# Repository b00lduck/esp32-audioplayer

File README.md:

# esp32-audioplayer
ESP32 based MP3 audio player with RFID control and case made from laser cutted plywood

!!! WORK IN PROGRESS !!!
!!! not functional yet !!!

## Used electronic hardware components:
* ESP32 NodeMCU module
* RFID-RC522 module (i.e. https://www.ebay.de/itm/172603664748)
* VS1053B module with SD-slot (i.e. http://www.ebay.de/itm/272761135002)
* Mifare classic 13.56MHz RFID cards (clones will do the job too, i.e. http://www.ebay.de/itm/122525501095)
* Adafruit PowerBoost 500 Charger module
* 3.7V LiPo battery 
* Class-D amplifier module
* SD-Card (i.e. 4GB)
* two Visaton FR7 (4 ohms) speakers
* Custom main board (see kicad folder for layout)
* Custom panel board (see kicad folder for layout)
* 1x 220uF 35V
* 1x 1uF 63V
* 4x 100nF 
* 2x 47nF
* 1x resistor ladder 4x 4.7k
* 1x 10R 
* 1x 10kR
* 1x 22kR
* 4x WSL10 (2x5 header 2.54mm with notch)
* 2x 2-pin header 2.54mm
* 4x 4-pin header 2.54mm
* some wire for airwires
* some insulated wire 1mm², red and black (for internal connections)
* 1x USB 2 Micro-B connector
* 1x power switch
* 1x USB 2 micro cable (for internal connection)
* optional: MEMS gyroscope module
* optional: 0.96 inch I2C OLED display

## Wood parts:
* 6 sheets, one for every side of the case
* 2 distance rings for the speakers

## Metal parts:
* 2x 100x75x0.8mm aluminium sheet

## 3D-Printed parts:
* 8x inner edge reinforcements
* 4x M3x3 standoff
* 8x M3*8 standoff (for main board)
* 4x M3x11 standoff (for MP3 board)
* 2x M3x6 standoff (for panel board)
* 2x M3x4 standoff (for panel board)
* 1x USB receptacle holder
* 1x SD-Card slot box
* 1x SD-Card slot cover

## Screws
* 4x M3x25 DIN 7991/ISO 10642 (countersunk allen bolt)
* 32x M3 DIN 934/ISO 4042 (nut)
* 8x M3 DIN 125/ISO 7089 (washer)
* 8x M3x20 DIN 912/ISO 4762 (cylinder head allen bolt)
* 2x M2x10 DIN 912/ISO 4762 (cylinder head allen bolt) for amp
* 2x M2 DIN 934/ISO 4042 (nut)
* 2x M2 DIN 125/ISO 7089 (washer)
* 8x M3x?? DIN 7991/ISO 10642 (countersunk allen bolt) for speakers
* 24x M3x15 DIN 7991/ISO 10642 (countersunk allen bolt) for inner corners

## Used software:
* VSCode with PlatformioIDE

## Used Arduino Libraries:
* SdFat 1.0.7
* MFRC522 1.3.6

## Port mapping
see src/config.h

## 3D printing
I used black 1.75 PETG filament for all parts.
Layer height was 0.15mm at a printing speed of 30mm/s.

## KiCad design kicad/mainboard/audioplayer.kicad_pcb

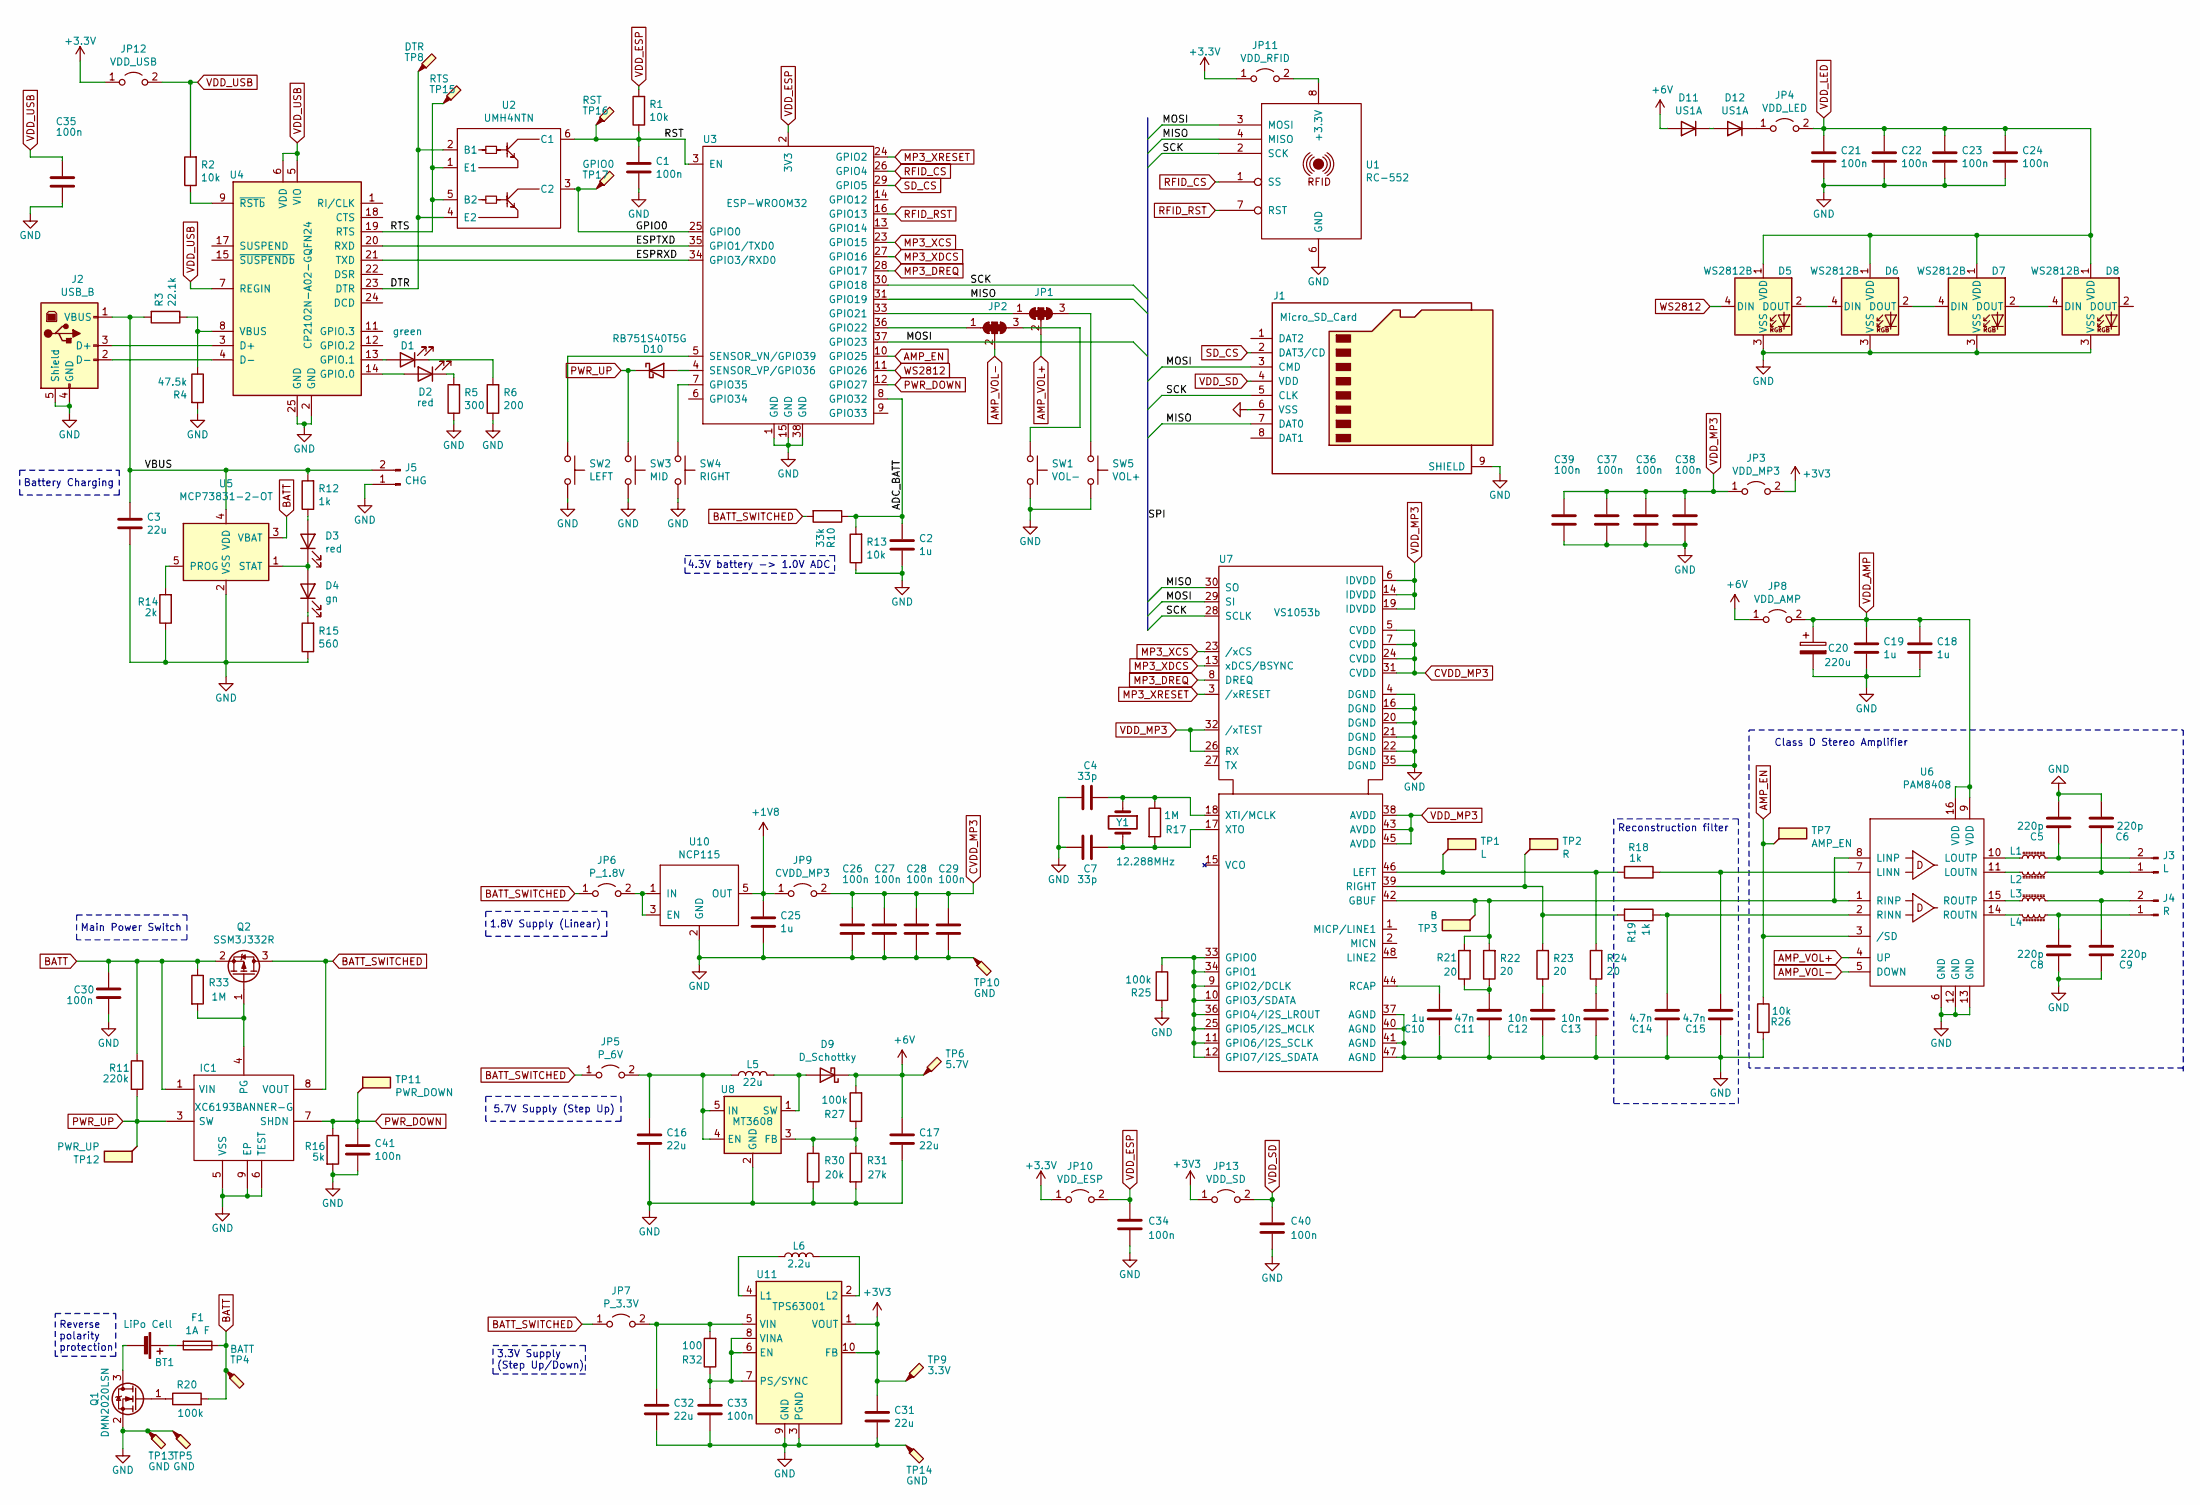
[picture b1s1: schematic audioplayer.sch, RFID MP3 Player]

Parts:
BT1: LiPo Cell; PinHeader_1x02_P2.54mm_Vertical
C1, C21, C22, C23, C24, C26, C27, C28, C29, C30, C33, C34, C35, C36, C37, C38, C39, C40, C41: 100n; C_0603_1608Metric
C2, C10, C18, C19, C25: 1u; C_0805_2012Metric; Mouser 963-EMK212B7105KG-T
C3, C16, C17, C31, C32: 22u; C_1210_3225Metric; Mouser 963-EMK325B7226MMHP
C4, C7: 33p; C_0603_1608Metric
C5, C6, C8, C9: 220p; C_0603_1608Metric
C11: 47n; C_0805_2012Metric; Mouser 80-C0805C473J3GEAULR
C12, C13: 10n; C_0603_1608Metric; Mouser 81-GRM1885C1E103JA1D
C14, C15: 4.7n; C_0603_1608Metric; Farnell 2906783
C20: 220u; CP_Radial_D8.0mm_P3.50mm
D1: green; LED_0805_2012Metric; Farnell 1318243
D2: red; LED_0805_2012Metric; Farnell 1318244
D3: red; LED_0805_2012Metric; Farnell 1318243
D4: gn; LED_0805_2012Metric; Farnell 1318244
D5, D6, D7, D8: WS2812B; LED_WS2812B_PLCC4_5.0x5.0mm_P3.2mm
D9: D_Schottky; D_SMA; Farnell 2211964
D10: RB751S40T5G; D_SOD-523; Farnell 2211964
D11, D12: US1A; D_SMA
F1: 1A F; Fuse_Littelfuse_372_D8.50mm
IC1: XC6193BANNER-G; XC6192AA05ERG
J1: Micro_SD_Card; microSD_HC_Hirose_DM3AT-SF-PEJM5; Farnell 1764374
J2: USB_B; USB_B_Lumberg_2411_02_Horizontal; Farnell 1308876
J3: L; PinHeader_1x02_P2.54mm_Vertical
J4: R; PinHeader_1x02_P2.54mm_Vertical
J5: CHG; PinHeader_1x02_P2.54mm_Vertical
JP1, JP2: SolderJumper_3_Bridged123; SolderJumper-3_P1.3mm_Open_RoundedPad1.0x1.5mm_NumberLabels
JP3: VDD_MP3; SolderJumper-2_P1.3mm_Open_RoundedPad1.0x1.5mm
JP4: VDD_LED; SolderJumper-2_P1.3mm_Open_RoundedPad1.0x1.5mm
JP5: P_6V; SolderJumper-2_P1.3mm_Open_RoundedPad1.0x1.5mm
JP6: P_1.8V; SolderJumper-2_P1.3mm_Open_RoundedPad1.0x1.5mm
JP7: P_3.3V; SolderJumper-2_P1.3mm_Open_RoundedPad1.0x1.5mm
JP8: VDD_AMP; SolderJumper-2_P1.3mm_Open_RoundedPad1.0x1.5mm
JP9: CVDD_MP3; SolderJumper-2_P1.3mm_Open_RoundedPad1.0x1.5mm
JP10: VDD_ESP; SolderJumper-2_P1.3mm_Open_RoundedPad1.0x1.5mm
JP11: VDD_RFID; SolderJumper-2_P1.3mm_Open_RoundedPad1.0x1.5mm
JP12: VDD_USB; SolderJumper-2_P1.3mm_Open_RoundedPad1.0x1.5mm
JP13: VDD_SD; SolderJumper-2_P1.3mm_Open_RoundedPad1.0x1.5mm
L1, L2, L3, L4: 600; L_0805_2012Metric; Farnell 1635719
L5: 22u; L_Taiyo-Yuden_NR-60xx; Mouser 963-NR6028T220M
L6: 2.2u; L_Taiyo-Yuden_NR-60xx; Mouser 963-NR6028T2R2N
Q1: DMN2020LSN; SC-59; Farnell 2543536
Q2: SSM3J332R; SOT-23
R1, R2, R13, R26: 10k; R_0603_1608Metric
R3: 22.1k; R_1206_3216Metric; Mouser 71-CRCW120622K1FKEAC
R4: 47.5k; R_1206_3216Metric; Mouser 71-CRCW120647K5FKEAC
R5: 300; R_0603_1608Metric
R6: 200; R_0603_1608Metric
R10: 33k; R_0603_1608Metric
R11: 220k; R_0603_1608Metric
R12, R18, R19: 1k; R_0603_1608Metric
R14: 2k; R_0603_1608Metric
R15: 560; R_0603_1608Metric
R16: 5k; R_0603_1608Metric
R17, R33: 1M; R_0603_1608Metric
R20, R25, R27: 100k; R_0603_1608Metric
R21, R22, R23, R24: 20; R_0603_1608Metric
R30: 20k; R_0603_1608Metric
R31: 27k; R_0603_1608Metric
R32: 100; R_0603_1608Metric
SW1: VOL-; SW_Tactile_Straight_KSA0Axx1LFTR; Farnell 2468761
SW2: LEFT; SW_Tactile_Straight_KSA0Axx1LFTR; Farnell 2468761
SW3: MID; SW_Tactile_Straight_KSA0Axx1LFTR; Farnell 2468761
SW4: RIGHT; SW_Tactile_Straight_KSA0Axx1LFTR; Farnell 2468761
SW5: VOL+; SW_Tactile_Straight_KSA0Axx1LFTR; Farnell 2468761
TP1: L; TestPoint_Pad_D1.5mm
TP2: R; TestPoint_Pad_D1.5mm
TP3: B; TestPoint_Pad_D1.5mm
TP4: BATT; TestPoint_Pad_D1.5mm
TP5, TP10, TP13, TP14: GND; TestPoint_Pad_D1.5mm
TP6: 5.7V; TestPoint_Pad_D1.5mm
TP7: AMP_EN; TestPoint_Pad_D1.5mm
TP8: DTR; TestPoint_Pad_D1.5mm
TP9: 3.3V; TestPoint_Pad_D1.5mm
TP11: PWR_DOWN; TestPoint_Pad_D1.5mm
TP12: PWR_UP; TestPoint_Pad_D1.5mm
TP15: RTS; TestPoint_Pad_D1.5mm
TP16: RST; TestPoint_Pad_D1.5mm
TP17: GPIO0; TestPoint_Pad_D1.5mm
U1: RC-552; RFID-RC522
U2: UMH4NTN; SOT-363_SC-70-6; Farnell 1680405
U3: ESP-WROOM32; ESP32-WROOM
U4: CP2102N-A02-GQFN24; QFN-24-1EP_4x4mm_P0.5mm_EP2.6x2.6mm; Mouser 634-CP2102NA02GQFN24
U5: MCP73831-2-OT; SOT-23-5; Farnell 1332158
U6: PAM8408; SO-16_5.3x10.2mm_P1.27mm; Mouser 621-PAM8408DR
U7: VS1053b; LQFP-48_7x7mm_P0.5mm
U8: MT3608; SOT-23-6
U10: NCP115; TSOP-5_1.65x3.05mm_P0.95mm; Farnell 2981135
U11: TPS63001; Texas_DRC0010J_ThermalVias; Farnell 3008242
Y1: 12.288MHz; Crystal_SMD_ABLS7M; Farnell 3228382

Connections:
+1V8: C25.1, JP9.1 (A), U10.5 (OUT)
+6V: C17.1, D9.1 (K), D11.2 (A), JP8.1 (A), R27.2, TP6.1
/ADC_BATT: C2.1, R10.1, R13.2, U3.8 (GPIO32)
/DTR: TP8.1, U2.2 (B1), U2.4 (E2), U4.23 (DTR)
/ESPRXD: U3.34 (GPIO3/RXD0), U4.21 (TXD)
/ESPTXD: U3.35 (GPIO1/TXD0), U4.20 (RXD)
/GPIO0: TP17.1, U2.3 (C2), U3.25 (GPIO0)
/MISO: J1.7 (DAT0), U1.4 (MISO), U3.31 (GPIO19), U7.30 (SO)
/MOSI: J1.3 (CMD), U1.3 (MOSI), U3.37 (GPIO23), U7.29 (SI)
/RST: C1.1, R1.1, TP16.1, U2.6 (C1), U3.3 (EN)
/RTS: TP15.1, U2.1 (E1), U2.5 (B2), U4.19 (RTS)
/SCK: J1.5 (CLK), U1.2 (SCK), U3.30 (GPIO18), U7.28 (SCLK)
/VBUS: C3.1, J2.1 (VBUS), J5.2, R3.2, R12.2, U5.4 (VDD)
AMP_EN: R26.1, TP7.1, U3.10 (GPIO25), U6.3 (/SD)
AMP_VOL+: JP1.2 (C), U6.4 (UP)
AMP_VOL-: JP2.2 (C), U6.5 (DOWN)
BATT: C30.1, F1.1, IC1.1 (VIN), Q2.2 (S), R11.1, R20.2, R33.1, TP4.1, U5.3 (VBAT)
BATT_SWITCHED: IC1.8 (VOUT), JP5.1 (A), JP6.1 (A), JP7.1 (A), Q2.3 (D), R10.2
CVDD_MP3: C26.1, C27.1, C28.1, C29.1, JP9.2 (B), U7.5 (CVDD), U7.7 (CVDD), U7.24 (CVDD), U7.31 (CVDD)
GND: C1.2, C2.2, C3.2, C4.1, C5.2, C6.2, C7.1, C8.1, C9.1, C10.1, C11.1, C12.1, C13.1, C14.1, C15.1, C16.2, C17.2, C18.2, C19.2, C20.2, C21.2, C22.2, C23.2, C24.2, C25.2, C26.2, C27.2, C28.2, C29.2, C30.2, C31.2, C32.2, C33.2, C34.2, C35.2, C36.2, C37.2, C38.2, C39.2, C40.2, C41.2, D5.3 (VSS), D6.3 (VSS), D7.3 (VSS), D8.3 (VSS), IC1.5 (VSS), IC1.6 (TEST), IC1.9 (EP), J1.6 (VSS), J1.9 (SHIELD), J2.4 (GND), J2.5 (Shield), J5.1, Q1.2 (S), R4.2, R5.1, R6.1, R13.1, R14.1, R15.1, R16.2, R25.2, R26.2, R30.2, R31.2, SW1.2, SW2.1, SW3.1, SW4.2, SW5.2, TP5.1, TP10.1, TP13.1, TP14.1, U1.6 (GND), U3.1 (GND), U3.15 (GND), U3.38 (GND), U4.2 (GND), U4.25 (GND), U5.2 (VSS), U6.6 (GND), U6.12 (GND), U6.13 (GND), U7.4 (DGND), U7.16 (DGND), U7.20 (DGND), U7.21 (DGND), U7.22 (DGND), U7.35 (DGND), U7.37 (AGND), U7.40 (AGND), U7.41 (AGND), U7.47 (AGND), U8.2 (GND), U10.2 (GND), U11.3 (PGND), U11.9 (GND), U11.11 (PGND)
MP3_DREQ: U3.28 (GPIO17), U7.8 (DREQ)
MP3_XCS: U3.23 (GPIO15), U7.23 (/xCS)
MP3_XDCS: U3.27 (GPIO16), U7.13 (xDCS/BSYNC)
MP3_XRESET: U3.24 (GPIO2), U7.3 (/xRESET)
unnamed: BT1.1 (+), F1.2
unnamed: BT1.2 (-), Q1.3 (D)
unnamed: C4.2, R17.1, U7.18 (XTI/MCLK), Y1.1
unnamed: C5.1, J3.2, L1.2
unnamed: C6.1, J3.1, L2.1
unnamed: C7.2, R17.2, U7.17 (XTO), Y1.2
unnamed: C8.2, J4.1, L4.1
unnamed: C9.2, J4.2, L3.2
unnamed: C10.2, U7.44 (RCAP)
unnamed: C11.2, R21.1, R22.1
unnamed: C12.2, R23.1
unnamed: C13.2, R24.1
unnamed: C14.2, R19.1, U6.2 (RINN)
unnamed: C15.2, R18.1, U6.7 (LINN)
unnamed: C16.1, JP5.2 (B), L5.1, U8.4 (EN), U8.5 (IN)
unnamed: C32.1, JP7.2 (B), R32.2, U11.5 (VIN)
unnamed: C33.1, R32.1, U11.6 (EN), U11.7 (PS/SYNC), U11.8 (VINA)
unnamed: D1.1 (K), R6.2
unnamed: D1.2 (A), U4.13 (GPIO.1)
unnamed: D2.1 (K), R5.2
unnamed: D2.2 (A), U4.14 (GPIO.0)
unnamed: D3.1 (K), D4.2 (A), U5.1 (STAT)
unnamed: D3.2 (A), R12.1
unnamed: D4.1 (K), R15.2
unnamed: D5.2 (DOUT), D6.4 (DIN)
unnamed: D6.2 (DOUT), D7.4 (DIN)
unnamed: D7.2 (DOUT), D8.4 (DIN)
unnamed: D9.2 (A), L5.2, U8.1 (SW)
unnamed: D10.2 (A), U3.4 (SENSOR_VP/GPIO36)
unnamed: D11.1 (K), D12.2 (A)
unnamed: D12.1 (K), JP4.1 (A)
unnamed: IC1.4 (PG), Q2.1 (G), R33.2
unnamed: J2.2 (D-), U4.4 (D-)
unnamed: J2.3 (D+), U4.3 (D+)
unnamed: JP1.1 (A), U3.33 (GPIO21)
unnamed: JP1.3 (B), SW5.1
unnamed: JP2.1 (A), U3.36 (GPIO22)
unnamed: JP2.3 (B), SW1.1
unnamed: JP6.2 (B), U10.1 (IN), U10.3 (EN)
unnamed: JP11.2 (B), U1.8 (+3.3V)
unnamed: L1.1, U6.10 (LOUTP)
unnamed: L2.2, U6.11 (LOUTN)
unnamed: L3.1, U6.15 (ROUTP)
unnamed: L4.2, U6.14 (ROUTN)
unnamed: L6.1, U11.4 (L1)
unnamed: L6.2, U11.2 (L2)
unnamed: Q1.1 (G), R20.1
unnamed: R2.1, U4.9 (~RSTb)
unnamed: R3.1, R4.1, U4.8 (VBUS)
unnamed: R14.2, U5.5 (PROG)
unnamed: R18.2, R24.2, TP1.1, U7.46 (LEFT)
unnamed: R19.2, R23.2, TP2.1, U7.39 (RIGHT)
unnamed: R21.2, R22.2, TP3.1, U6.1 (RINP), U6.8 (LINP), U7.42 (GBUF)
unnamed: R25.1, U7.9 (GPIO2/DCLK), U7.10 (GPIO3/SDATA), U7.11 (GPIO6/I2S_SCLK), U7.12 (GPIO7/I2S_SDATA), U7.25 (GPIO5/I2S_MCLK), U7.33 (GPIO0), U7.34 (GPIO1), U7.36 (GPIO4/I2S_LROUT)
unnamed: R27.1, R30.1, R31.1, U8.3 (FB)
unnamed: SW2.2, U3.5 (SENSOR_VN/GPIO39)
unnamed: SW4.1, U3.7 (GPIO35)
PWR_DOWN: C41.1, IC1.7 (SHDN), R16.1, TP11.1, U3.12 (GPIO27)
PWR_UP: D10.1 (K), IC1.3 (SW), R11.2, SW3.2, TP12.1
RFID_CS: U1.1 (SS), U3.26 (GPIO4)
RFID_RST: U1.7 (RST), U3.16 (GPIO13)
SD_CS: J1.2 (DAT3/CD), U3.29 (GPIO5)
VDD_AMP: C18.1, C19.1, C20.1, JP8.2 (B), U6.9 (VDD), U6.16 (VDD)
VDD_ESP: C34.1, JP10.2 (B), R1.2, U3.2 (3V3)
VDD_LED: C21.1, C22.1, C23.1, C24.1, D5.1 (VDD), D6.1 (VDD), D7.1 (VDD), D8.1 (VDD), JP4.2 (B)
VDD_MP3: C36.1, C37.1, C38.1, C39.1, JP3.1 (A), U7.6 (IDVDD), U7.14 (IDVDD), U7.19 (IDVDD), U7.26 (RX), U7.32 (/xTEST), U7.38 (AVDD), U7.43 (AVDD), U7.45 (AVDD)
VDD_SD: C40.1, J1.4 (VDD), JP13.2 (B)
VDD_USB: C35.1, JP12.2 (B), R2.2, U4.5 (VIO), U4.6 (VDD), U4.7 (REGIN)
WS2812: D5.4 (DIN), U3.11 (GPIO26)

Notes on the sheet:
4.3V battery -> 1.0V ADC
Reconstruction filter
Class D Stereo Amplifier
Battery Charging
5.7V Supply (Step Up)
1.8V Supply (Linear)
3.3V Supply (Step Up/Down)
Reverse polarity protection
Main Power Switch

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
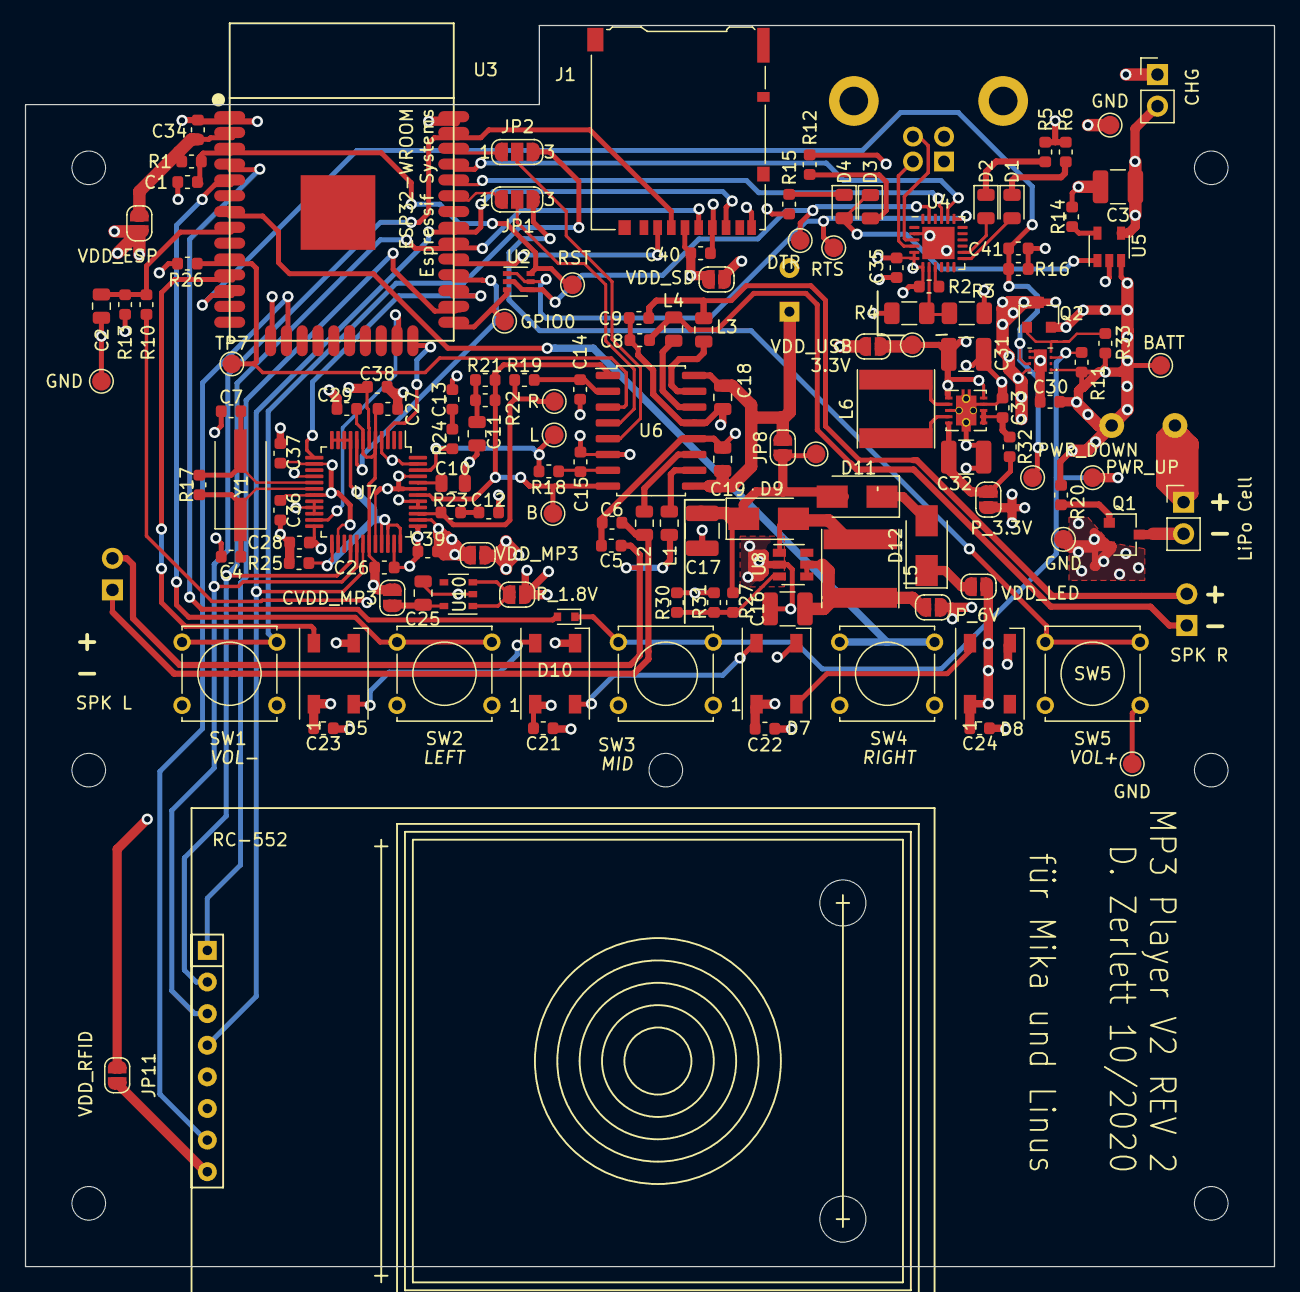
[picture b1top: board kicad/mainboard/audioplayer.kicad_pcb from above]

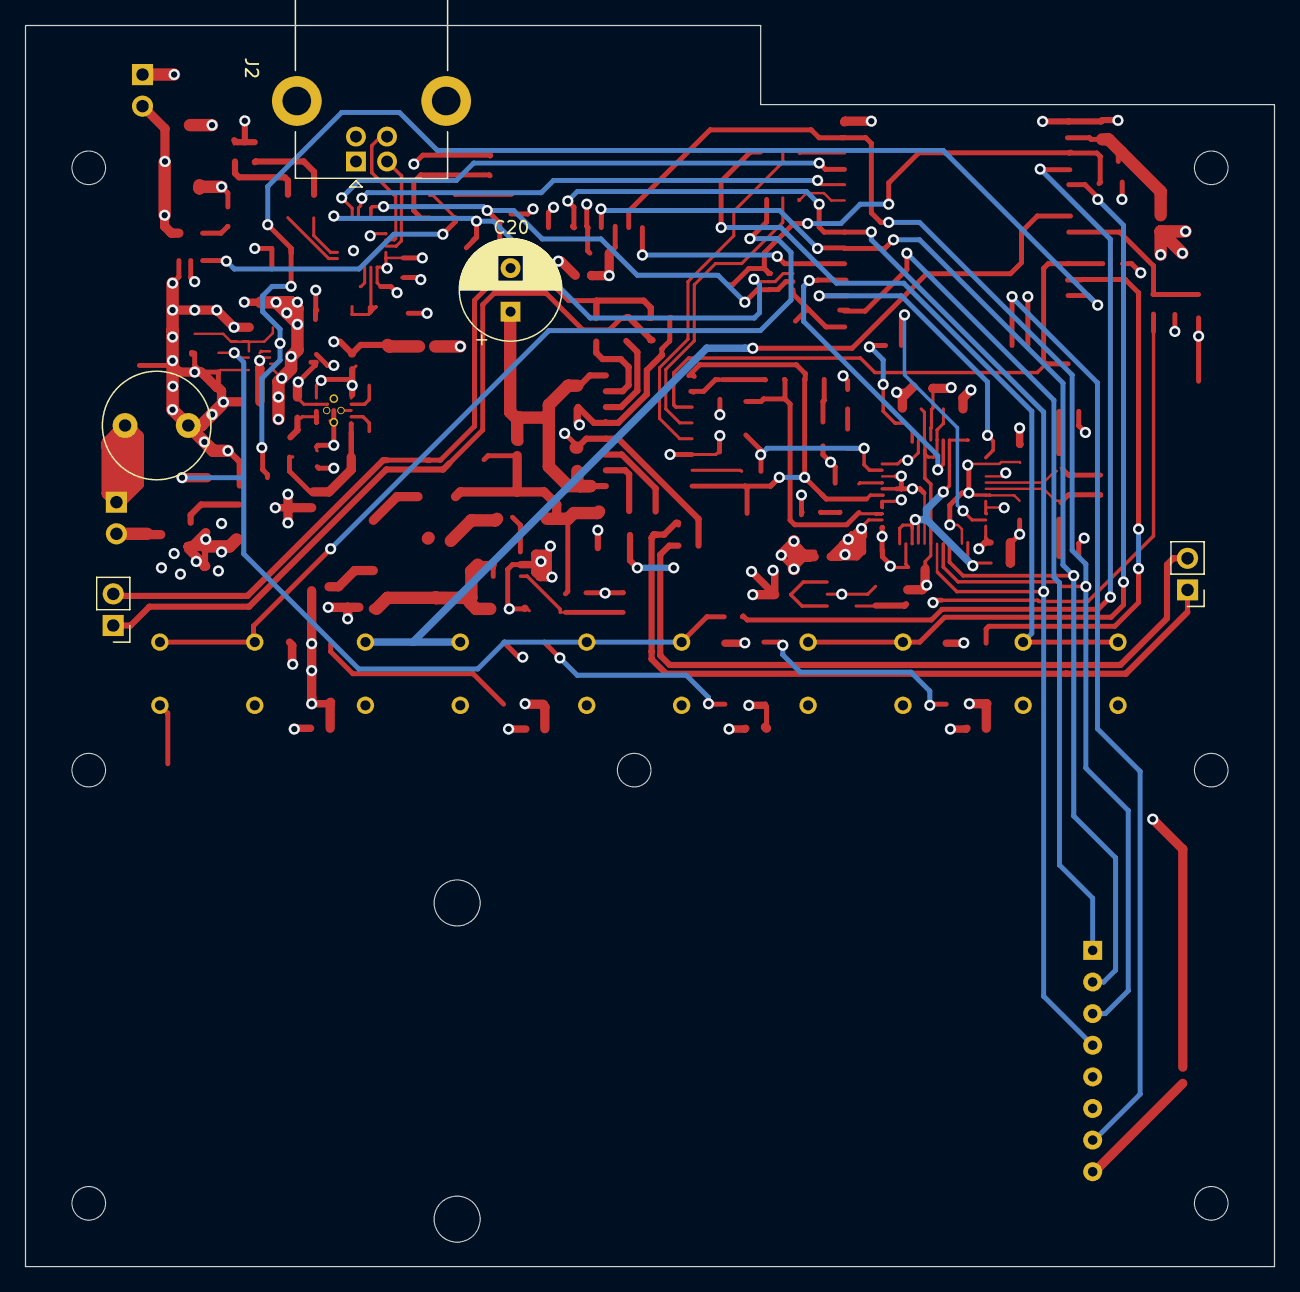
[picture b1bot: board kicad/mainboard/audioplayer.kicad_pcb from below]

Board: 4 copper layers, 100.3 x 99.7 mm, 143 parts (5 on the bottom side), 94 nets.

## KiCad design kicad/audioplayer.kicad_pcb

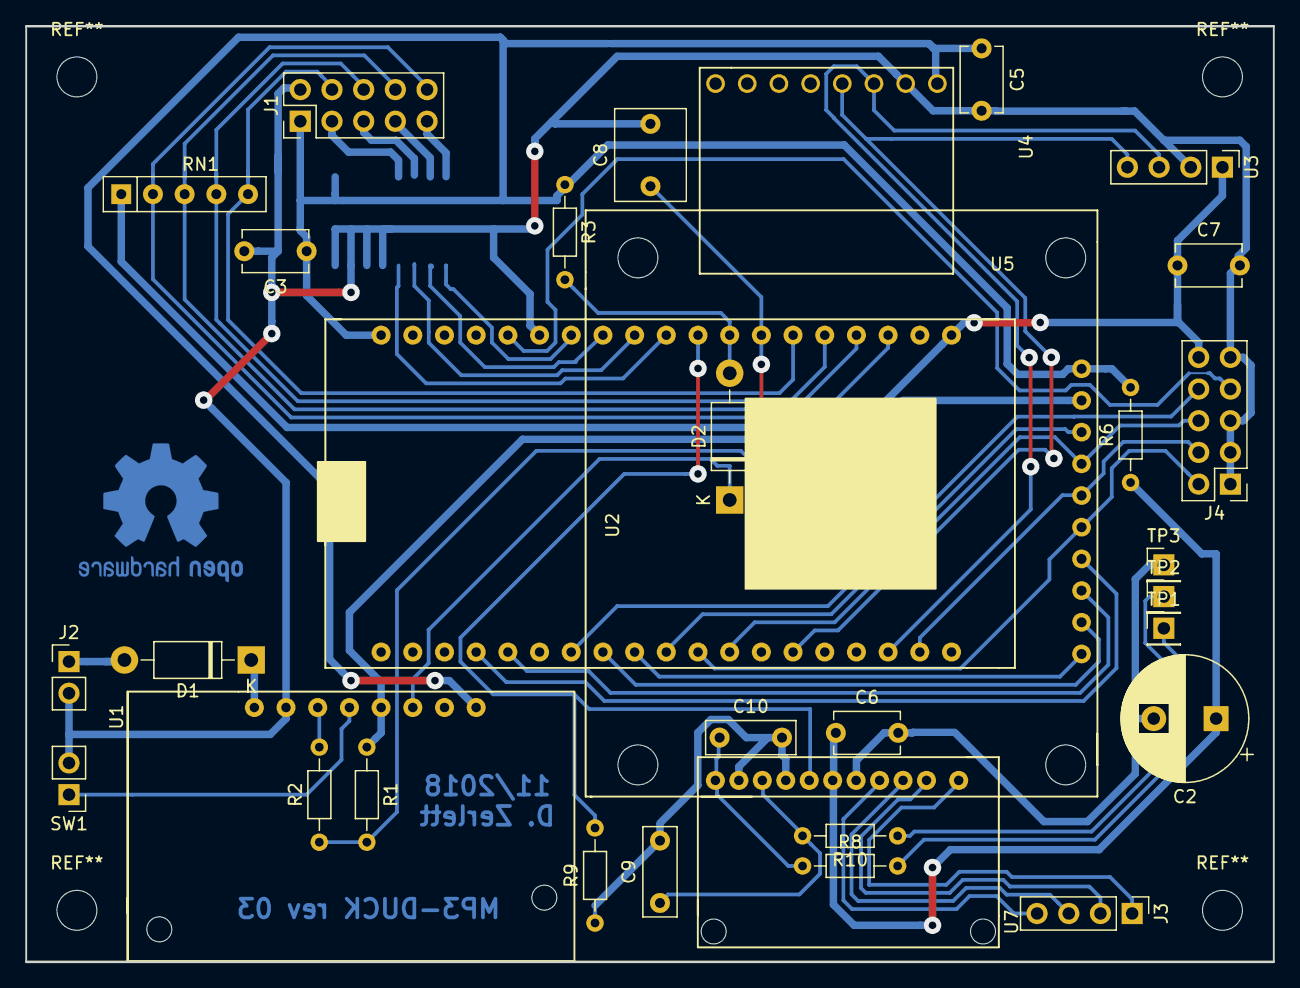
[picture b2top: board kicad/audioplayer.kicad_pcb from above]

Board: 2 copper layers, 100.0 x 75.0 mm, 33 parts (1 on the bottom side), 45 nets.

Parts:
C2: 100u; CP_Radial_D10.0mm_P5.00mm
C3, C5, C7: C; C_Disc_D5.1mm_W3.2mm_P5.00mm
C6: 100n; C_Disc_D5.1mm_W3.2mm_P5.00mm
C8: 1u; C_Rect_L7.2mm_W5.5mm_P5.00mm_FKS2_FKP2_MKS2_MKP2
C9, C10: 4.7n; C_Rect_L7.0mm_W2.5mm_P5.00mm
D1, D2: 1N4007; D_DO-41_SOD81_P10.16mm_Horizontal
J1: Panel; PinHeader_2x05_P2.54mm_Vertical
J2: Charge_USB; PinHeader_1x02_P2.54mm_Vertical
J3: SPK; PinHeader_1x04_P2.54mm_Vertical
J4: RFID; PinHeader_2x05_P2.54mm_Vertical
R1, R3: 10k; R_Axial_DIN0204_L3.6mm_D1.6mm_P7.62mm_Horizontal
R2: 33k; R_Axial_DIN0204_L3.6mm_D1.6mm_P7.62mm_Horizontal
R6: 10; R_Axial_DIN0204_L3.6mm_D1.6mm_P7.62mm_Horizontal
R8, R10: 1k; R_Axial_DIN0204_L3.6mm_D1.6mm_P7.62mm_Horizontal
R9: 22k; R_Axial_DIN0204_L3.6mm_D1.6mm_P7.62mm_Horizontal
RN1: R_Network04; R_Array_SIP5
SW1: POWER; PinHeader_1x02_P2.54mm_Vertical
TP1: R; PinHeader_1x01_P2.54mm_Vertical
TP2: L; PinHeader_1x01_P2.54mm_Vertical
TP3: GNDA; PinHeader_1x01_P2.54mm_Vertical
U1: PB-500; adafruit-pb500-charge
U2: ESP32-nodeMCU; esp32-nodemcu-noholes
U3: OLED; PinHeader_1x04_P2.54mm_Vertical
U4: GY-521; gy-521-noholes
U5: VS1053/SD_breakout; vs1053_breakout_upside_down
U6: ULN2003; SOIC-16W_5.3x10.2mm_P1.27mm
U7: HW-323; hw-323

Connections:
+3V3: C7.1, J4.10, RN1.1, U2.1, U3.1
+5V: C3.1, C5.1, J1.1, R3.1, R6.2, U1.8, U2.19, U4.1, U5.1, U6.9
+5VA: C2.1, C6.1, R6.1, U7.6
/ADC_BATT: C8.1, R1.2, R2.1, U2.7
/AMP_ENABLE: R9.2, U2.9, U7.7
/LED1_OD: J1.9, U6.16
/LED2_OD: J1.7, U6.15
/LED3_OD: J1.5, U6.14
/LED4_OD: J1.3, U6.13
/LOW_BATT: D2.1, U1.6
/MISO: J4.6, U2.31, U5.4
/MOSI: J4.4, U2.37, U5.5
/MP3_DREQ: U2.28, U5.10
/MP3_XCS: U2.23, U5.7
/MP3_XDCS: U2.27, U5.9
/MP3_XRESET: U2.24, U5.8
/RST: J4.7, U2.15
/SCK: J4.2, U2.30, U5.6
/SCL: U2.36, U3.3, U4.3
/SDA: U2.33, U3.4, U4.4
/SD_CS: U2.29, U5.3
/SS: J4.8, U2.26
GND: C3.2, C5.2, C7.2, C8.2, J1.2, J2.2, J4.1, J4.3, J4.5, J4.9, R1.1, SW1.2, U1.2, U1.5, U2.14, U3.2, U4.2, U5.2, U6.5, U6.6, U6.7, U6.8
GNDA: C2.2, C6.2, C9.2, C10.2, R9.1, TP3.1, U7.5, U7.8, U7.10
LED1: U2.10, U6.4
LED2: U2.11, U6.3
LED3: U2.12, U6.2
LED4: U2.13, U6.1
unnamed: C9.1, R10.2, U7.9
unnamed: C10.1, R8.1, U7.11
unnamed: D1.1, U1.1
unnamed: D1.2, J2.1
unnamed: D2.2, R3.2, U2.8
unnamed: J3.1, U7.1
unnamed: J3.2, U7.2
unnamed: J3.3, U7.3
unnamed: J3.4, U7.4
unnamed: R2.2, U1.3
unnamed: R8.2, TP1.1
unnamed: R10.1, TP2.1
unnamed: SW1.1, U1.4
SW1: J1.10, RN1.2, U2.3
SW2: J1.8, RN1.3, U2.4
SW3: J1.6, RN1.4, U2.5
SW4: J1.4, RN1.5, U2.6

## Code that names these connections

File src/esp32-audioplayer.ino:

/**
 * 
 * Copyright 2018 D.Zerlett <daniel@zerlett.eu>
 * 
 * This file is part of esp32-audioplayer.
 * 
 * esp32-audioplayer is free software: you can redistribute it and/or modify
 * it under the terms of the GNU General Public License as published by
 * the Free Software Foundation, either version 3 of the License, or
 * (at your option) any later version.
 *
 * esp32-audioplayer is distributed in the hope that it will be useful,
 * but WITHOUT ANY WARRANTY; without even the implied warranty of
 * MERCHANTABILITY or FITNESS FOR A PARTICULAR PURPOSE. See the
 * GNU General Public License for more details.
 *
 * You should have received a copy of the GNU General Public License
 * along with esp32-audioplayer. If not, see <http://www.gnu.org/licenses/>.
 *  
 */

#include <stdio.h>
#include <string.h>
#include <Wire.h>

#include "config.h"
#include "tools.h"
#include "buttons.h"
#include "VS1053.h"
#ifdef OLED
  #include "oled.h"
#endif
#include "rfid.h"
#include "sd.h"
#include "mapper.h"
#include "player.h"
#include "fatal.h"

VS1053          vs1053(VS1053_XCS_PIN, VS1053_XDCS_PIN, VS1053_DREQ_PIN, VS1053_XRESET_PIN);
RFID            rfid(MFRC522_CS_PIN, MFRC522_RST_PIN);
SDCard          sd(SD_CS_PIN);

#ifdef OLED
  Oled            oled(DISPLAY_ADDRESS);
  Fatal           fatal(oled);
  Player          player(fatal, oled, vs1053);
#else
  Fatal           fatal;
  Player          player(fatal, vs1053);
#endif

Mapper          mapper;
Buttons         buttons;

void setup() {

  Serial.begin(115200);                            
  Serial.println("\nStarting...");

  // Initialize GPIOs for LEDs
  // led1 green
  pinMode(LED1, OUTPUT);
  digitalWrite(LED1, LOW);
  
  // led2 white (player state)
  pinMode(LED2, OUTPUT);
  digitalWrite(LED2, LOW);
  
  // led3 red
//  pinMode(LED3, OUTPUT);
//  digitalWrite(LED3, LOW);

  // Initialize GPIOs for "amplifier enable"
  pinMode(AMP_ENABLE, OUTPUT);
  digitalWrite(AMP_ENABLE, LOW); 

  // Initialize buttons
  buttons.init();

  // Initialize GPIO for battery voltage
  pinMode(ADC_BATT, ANALOG);
  pinMode(LOW_BATT, INPUT);
  pinMode(SHUTDOWN, OUTPUT);
  digitalWrite(SHUTDOWN, LOW);

  Serial.println("GPIO init completed.");

  // Initialize I²C bus
  Wire.begin(I2C_SDA_PIN, I2C_SCL_PIN);
  #ifdef OLED
    oled.init();
    oled.loadingBar(0);  
  #endif  
  Wire.setClock(TWI_CLOCK);
  Serial.println("I²C init completed.");

  // Initialize SPI bus
  SPI.begin(SPI_SCK_PIN, SPI_MISO_PIN, SPI_MOSI_PIN);
  #ifdef OLED
    oled.loadingBar(25);
  #endif
  Serial.println("SPI init completed.");

  // Initialize RFID reader
  rfid.init();

  #ifdef OLED
    oled.loadingBar(50);
  #endif
  
  // Initialize SD card reader
  if (!sd.init()) {
      fatal.fatal("SD card error", "init failed");
  }

  Mapper::MapperError err = mapper.init(); 
  if (err != Mapper::MapperError::OK) {
    //player.play("/error.mp3");
    switch(err) {
      case Mapper::MapperError::MALFORMED_LINE_SYNTAX:
        fatal.fatal("Mapping error", "Syntax error");
      case Mapper::MapperError::MALFORMED_CARD_ID:
        fatal.fatal("Mapping error", "Illegal char in ID");
      case Mapper::MapperError::LINE_TOO_SHORT:
        fatal.fatal("Mapping error", "Line too short");    
      case Mapper::MapperError::LINE_TOO_LONG:
        fatal.fatal("Mapping error", "Line too long");
      case Mapper::MapperError::MAPPING_FILE_NOT_FOUND:
        fatal.fatal("Mapping error", "Mapping file not found");      
      case Mapper::MapperError::MALFORMED_FILE_NAME:
        fatal.fatal("Mapping error", "Malformed file name");   
      #ifdef FAIL_ON_FILE_NOT_FOUND      
        case Mapper::MapperError::REFERENCED_FILE_NOT_FOUND:
          fatal.fatal("Mapping error", "Referenced file not found");   
      #endif      
    }    
  }

  // initialize player
  player.init();

  player.play("/startup.mp3");

  oled.clear();  
}

uint16_t lpf = 0;


void loop() {

  bool changed = buttons.read();

  #ifdef OLED
  if (changed) {
    oled.buttons(buttons.state);
  }  
  #endif  

  // Cheapo one pole IIR low pass filter with unknown cutoff frequency (because sample rate is unknown).
  // This is good enough for battery monitoring though.
  //
  // lpf:
  // 0 is 0V battery voltage  
  // 1000 is approx. 4.12V battery voltage
  // in between linear (voltage divider)
  uint16_t batt = analogRead(ADC_BATT);
  uint16_t newLpf = (float)lpf * 0.95 + (float)batt * 0.05;
  lpf = newLpf;


  uint8_t lowBattFromPowerModule = digitalRead(LOW_BATT);
  if (lowBattFromPowerModule == 0) {
    pinMode(SHUTDOWN, OUTPUT);
    digitalWrite(SHUTDOWN, 1);
  }

  if (player.idleTime > 700000000) { // approx 15 min shutdown timer
    pinMode(SHUTDOWN, OUTPUT);
    digitalWrite(SHUTDOWN, 1);
  }
  
  // Volume Control
  if (buttons.buttonDown(0)) {
    player.increaseVolume();
  }

  if (buttons.buttonDown(2)) {
    player.decreaseVolume();
  }

  RFID::CardState cardState = rfid.checkCardState();
  
  switch(cardState) {
    case RFID::CardState::NEW_CARD:
      {
        char filename[MAX_FILENAME_STRING_LENGTH];
        Mapper::MapperError err = mapper.resolveIdToFilename(rfid.currentCard, filename);    
        switch(err) {
          case Mapper::MapperError::ID_NOT_FOUND:
            Serial.println(F("Card not found in mapping"));
            #ifdef OLED
              oled.trackName("Unknown card");
            #endif
            player.stop();        
          case Mapper::MapperError::LINE_TOO_LONG:
            fatal.fatal("Mapping error", "Long line/missing newline");         
          case Mapper::MapperError::MAPPING_FILE_NOT_FOUND:
            fatal.fatal("Mapping error", "Mapping file not found");         
          #ifdef FAIL_ON_FILE_NOT_FOUND  
            case Mapper::MapperError::REFERENCED_FILE_NOT_FOUND:
              fatal.fatal("Mapping error", "Data file not found"); 
          #endif              
          case OK:
            player.play(filename);
        } 
      }
      break;
    case RFID::CardState::REMOVED_CARD:
      Serial.println("removed card");
      player.stop();
      break;
    case RFID::CardState::FAULTY_CARD:
      Serial.println("faulty card");
      player.stop();
      break;
    case RFID::CardState::NO_CHANGE:
      break;
  }

  player.process();

}

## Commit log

2017-08-01 inital commit
2017-08-01 readme update
2017-08-10 license changed to GPLv3 use multiplexer for SPI CS lines
2017-08-10 multiplexing
2017-08-10 README code formatting
2017-08-10 README
2017-08-10 typo fix
2017-08-10 rfid enabled
2017-09-03 use 23017 gpio expander for CS lines
2017-09-03 README fix
2017-09-03 oled display
2017-09-11 added schematics
2017-11-03 loading bar and erro message, test mp3
2017-11-04 mapping file
2017-11-05 refactoring: pulled mapping out of main
2017-11-05 better error handling
2017-11-05 skip ID3v2 tag
2017-11-05 moved strings to flash
2017-11-07 comments
2017-11-11 Refactoring: pulled rfid out
2017-11-11 Refactoring: renaming to camelcase
2017-11-11 Refactoring: removed obsolete code
2017-11-11 refactoring: pulled out SDCard
2018-10-10 migrated to PlatformIO and ESP32
2018-10-10 gitignore
2018-10-10 rename main file
2018-10-10 fix serial params
2018-10-12 added libdeps
2018-10-12 buttons and leds
2018-10-28 volume control and amp standby
2018-11-03 schematic improvements
2018-11-05 case cut files
2018-11-05 kerf test pattern
2018-11-05 speaker ring
2018-11-06 card lid
2018-11-06 better card lid
2018-11-08 SD card slot improvements
2018-11-08 case improvements
2018-11-08 changed ring
2018-11-08 changed backside holes
2018-11-13 first board revision completed
2018-11-13 ADC code for battery monitoring, change GPIOs according to board
2018-11-14 fix board
2018-11-15 board improvements
2018-11-23 board rev 02
2018-11-30 board revision 03
    better ground handling, vastly reduced background noise
    added reconstruction filter to vs1053 output
    added possibillity to add headphone jack
    use smd darlington array
    add diode for battery low signal
    add diode for charging connector (reverse polarity protection just in case)
2018-12-02 3mm plexi case test
2018-12-02 kicad autosave
2018-12-02 fix kerf calculation
2018-12-05 Case changes: holes for inner corner reinforecemnts holes for RFID reader moved USB jack and power switch
2018-12-06 add 3.6mm pappel dxf
2018-12-07 3.6mm pappel fixes moved kicad software refactoring/preparations for wifi
2018-12-13 case fixes
2018-12-13 add panel board
2018-12-13 changed sd cut
2018-12-19 flipped holes for panel board
2018-12-19 standoffs
2018-12-19 standoffs for panel
2018-12-21 fix refactored software for new hardware
2019-01-26 case changes
2019-01-26 change nut spacing!
2019-02-17 board rev04
2019-03-13 case changed et al
2019-03-13 keller
2019-11-18 playlist support for folders
2020-06-08 change speaker grids
2020-06-08 usb b port
2020-06-08 kerf change
2020-06-19 add power management dropi-in board
2020-07-19 fix usb port size in case
2020-07-19 remove production files
2020-07-22 WIP new board
2020-07-22 programming circuit
2020-07-24 new board improvements
2020-08-05 new board WIP
2020-08-06 new board BOM consoldifation
2020-08-06 add board files
2020-08-10 board layout finalization
2020-08-10 board polish
2020-08-11 use zener diode array
2020-09-30 new board v1
2020-10-05 new board software first step
2020-10-22 software fixes for new board
2020-10-22 board v2-rev2
2020-12-09 v2 rev2
2021-01-16 WIP: refactor for HTTP control
2021-03-01 fix playlist handling
2021-03-04 admin interface card info
2021-03-05 card initialization
2021-03-07 file upload handling
2021-03-08 upload handling
2021-03-25 Read WIFI from NDEF card
2021-03-25 remove debug logging
2021-03-25 enable playback
2021-04-08 use new server
2021-04-09 cleanup
2021-05-06 sync, upload etc
2021-05-11 upload imporvements
2021-05-13 new file system driver, almost working
2021-05-13 fix file saving bug
2021-10-01 display FX, audio glitches
2021-12-15 lib updates minor fixes disabled file streaming
2021-12-15 fix card reading behaviour
2021-12-15 change card handling
2023-05-16 add card list functionality
